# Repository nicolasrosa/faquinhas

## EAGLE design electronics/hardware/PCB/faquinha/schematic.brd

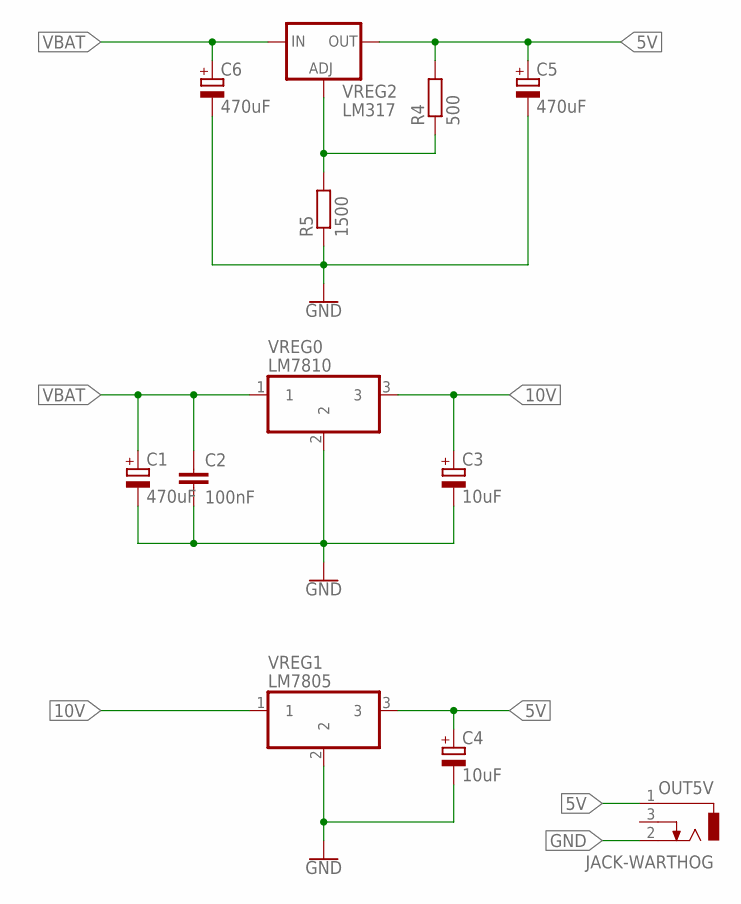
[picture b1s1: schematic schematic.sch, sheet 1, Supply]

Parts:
C1: 470uF; E3,5-8
C2: 100nF; C0805
C3, C4: 10uF; SMC_C
C5, C6: 470uF; SMC_C
OUT5V: JACK-WARTHOG
R4: 500; R0805
R5: 1500; R0805
VREG0: LM7810; TO220V-WARTHOG
VREG1: LM7805; TO220V-WARTHOG
VREG2: LM317; V-REG_DPACK

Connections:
5V: C4.+, C5.+, OUT5V.1, R4.2, VREG1.3, VREG2.4 (OUT); also elsewhere on the board
10V: C3.+, VREG0.3, VREG1.1; also elsewhere on the board
ADJ: R4.1, R5.2, VREG2.1 (ADJ)
GND: C1.-, C2.2, C3.-, C4.-, C5.-, C6.-, OUT5V.2 (3), R5.1, VREG0.2, VREG1.2; also elsewhere on the board
VBAT: C1.+, C2.1, C6.+, VREG0.1, VREG2.3 (IN); also elsewhere on the board

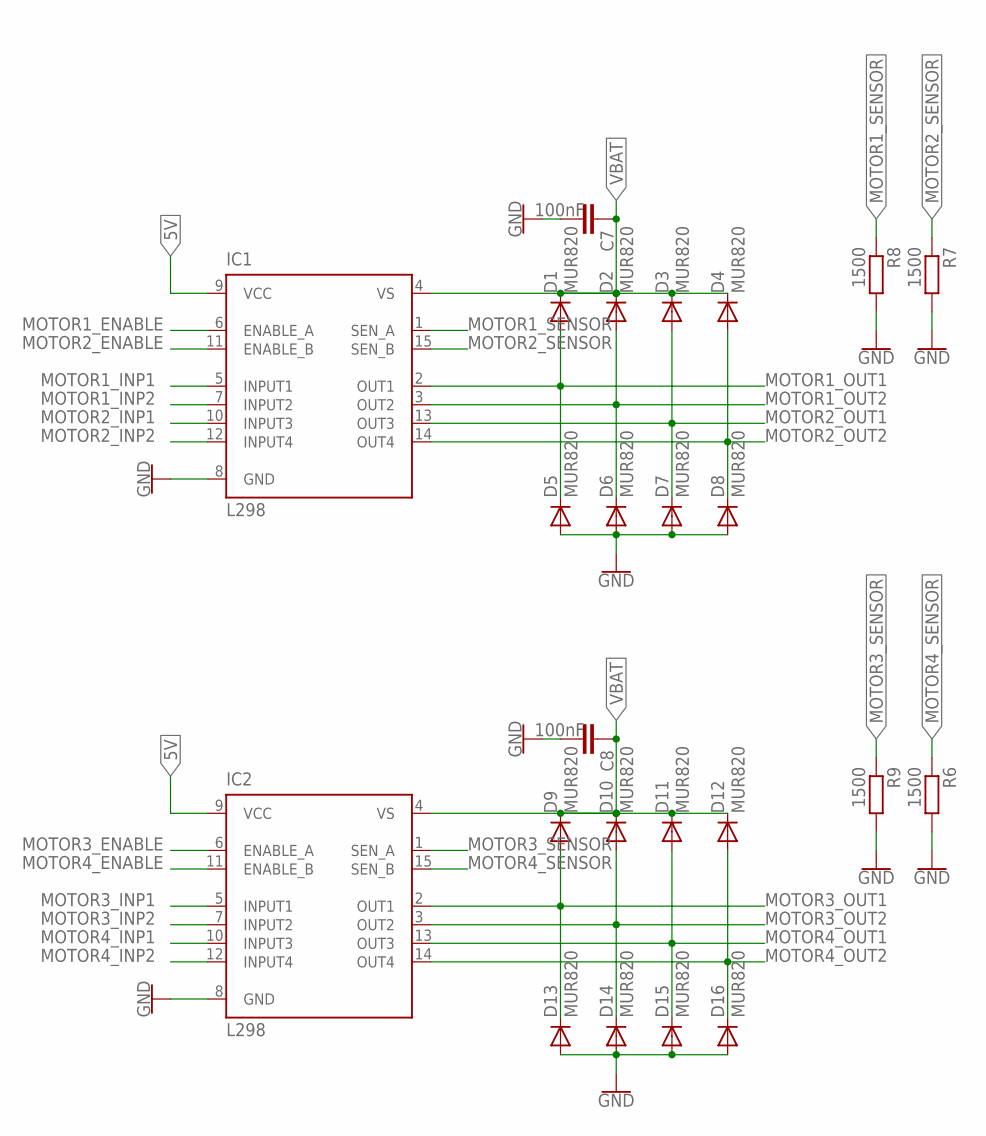
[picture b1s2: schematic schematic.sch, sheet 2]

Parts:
C7, C8: 100nF; C0805
D1, D2, D3, D4, D5, D6, D7, D8, D9, D10, D11, D12, D13, D14, D15, D16: MUR820; C221B1A
IC1, IC2: L298; MULTIWATT-15
R6, R7, R8, R9: 1500; R0805

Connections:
5V: IC1.9 (VCC), IC2.9 (VCC); also elsewhere on the board
GND: C7.2, C8.2, D5.A, D6.A, D7.A, D8.A, D13.A, D14.A, D15.A, D16.A, IC1.8 (GND), IC2.8 (GND), R6.2, R7.2, R8.2, R9.2; also elsewhere on the board
MOTOR1_ENABLE: IC1.6 (ENABLE_A)
MOTOR1_INP1: IC1.5 (INPUT1)
MOTOR1_INP2: IC1.7 (INPUT2)
MOTOR1_OUT1: D1.A, D5.C, IC1.2 (OUT1)
MOTOR1_OUT2: D2.A, D6.C, IC1.3 (OUT2)
MOTOR1_SENSOR: IC1.1 (SEN_A), R8.1
MOTOR2_ENABLE: IC1.11 (ENABLE_B)
MOTOR2_INP1: IC1.10 (INPUT3)
MOTOR2_INP2: IC1.12 (INPUT4)
MOTOR2_OUT1: D3.A, D7.C, IC1.13 (OUT3)
MOTOR2_OUT2: D4.A, D8.C, IC1.14 (OUT4)
MOTOR2_SENSOR: IC1.15 (SEN_B), R7.1
MOTOR3_ENABLE: IC2.6 (ENABLE_A)
MOTOR3_INP1: IC2.5 (INPUT1)
MOTOR3_INP2: IC2.7 (INPUT2)
MOTOR3_OUT1: D9.A, D13.C, IC2.2 (OUT1)
MOTOR3_OUT2: D10.A, D14.C, IC2.3 (OUT2)
MOTOR3_SENSOR: IC2.1 (SEN_A), R9.1
MOTOR4_ENABLE: IC2.11 (ENABLE_B)
MOTOR4_INP1: IC2.10 (INPUT3)
MOTOR4_INP2: IC2.12 (INPUT4)
MOTOR4_OUT1: D11.A, D15.C, IC2.13 (OUT3)
MOTOR4_OUT2: D12.A, D16.C, IC2.14 (OUT4)
MOTOR4_SENSOR: IC2.15 (SEN_B), R6.1
VBAT: C7.1, C8.1, D1.C, D2.C, D3.C, D4.C, D9.C, D10.C, D11.C, D12.C, IC1.4 (VS), IC2.4 (VS); also elsewhere on the board

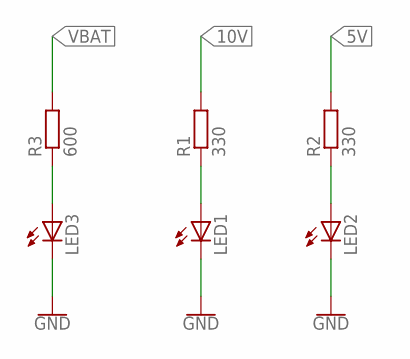
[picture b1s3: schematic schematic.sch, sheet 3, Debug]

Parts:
LED1, LED2, LED3: LEDCHIP-LED0805; CHIP-LED0805
R1, R2: 330; R0805
R3: 600; R0805

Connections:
5V: R2.2; also elsewhere on the board
10V: R1.2; also elsewhere on the board
GND: LED1.C, LED2.C, LED3.C; also elsewhere on the board
unnamed: LED1.A, R1.1
unnamed: LED2.A, R2.1
unnamed: LED3.A, R3.1
VBAT: R3.2; also elsewhere on the board

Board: 2 copper layers, 42 parts (0 on the bottom side), 20 nets, no tracks yet.

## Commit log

2017-09-16 [MOD] Initial Commit
2017-09-21 [MOD] Four motors working properly
2017-09-22 [MOD] Deu trampo, pra caralho
2017-09-22 [MOD] Deu trampo, pra caralho2
2017-09-23 [MOD] Multi Calibration working!
2017-09-23 [MOD] Vision migrated to BBB!
2017-09-23 [MOD] Main.py backup!

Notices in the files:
parts and their libraries:
SparkFun-IC-Power: Licensing: Creative Commons ShareAlike 4.0 International - https://creativecommons.org/licenses/by-sa/4.0
